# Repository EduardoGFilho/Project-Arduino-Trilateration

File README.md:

# Project-Arduino-Trilateration

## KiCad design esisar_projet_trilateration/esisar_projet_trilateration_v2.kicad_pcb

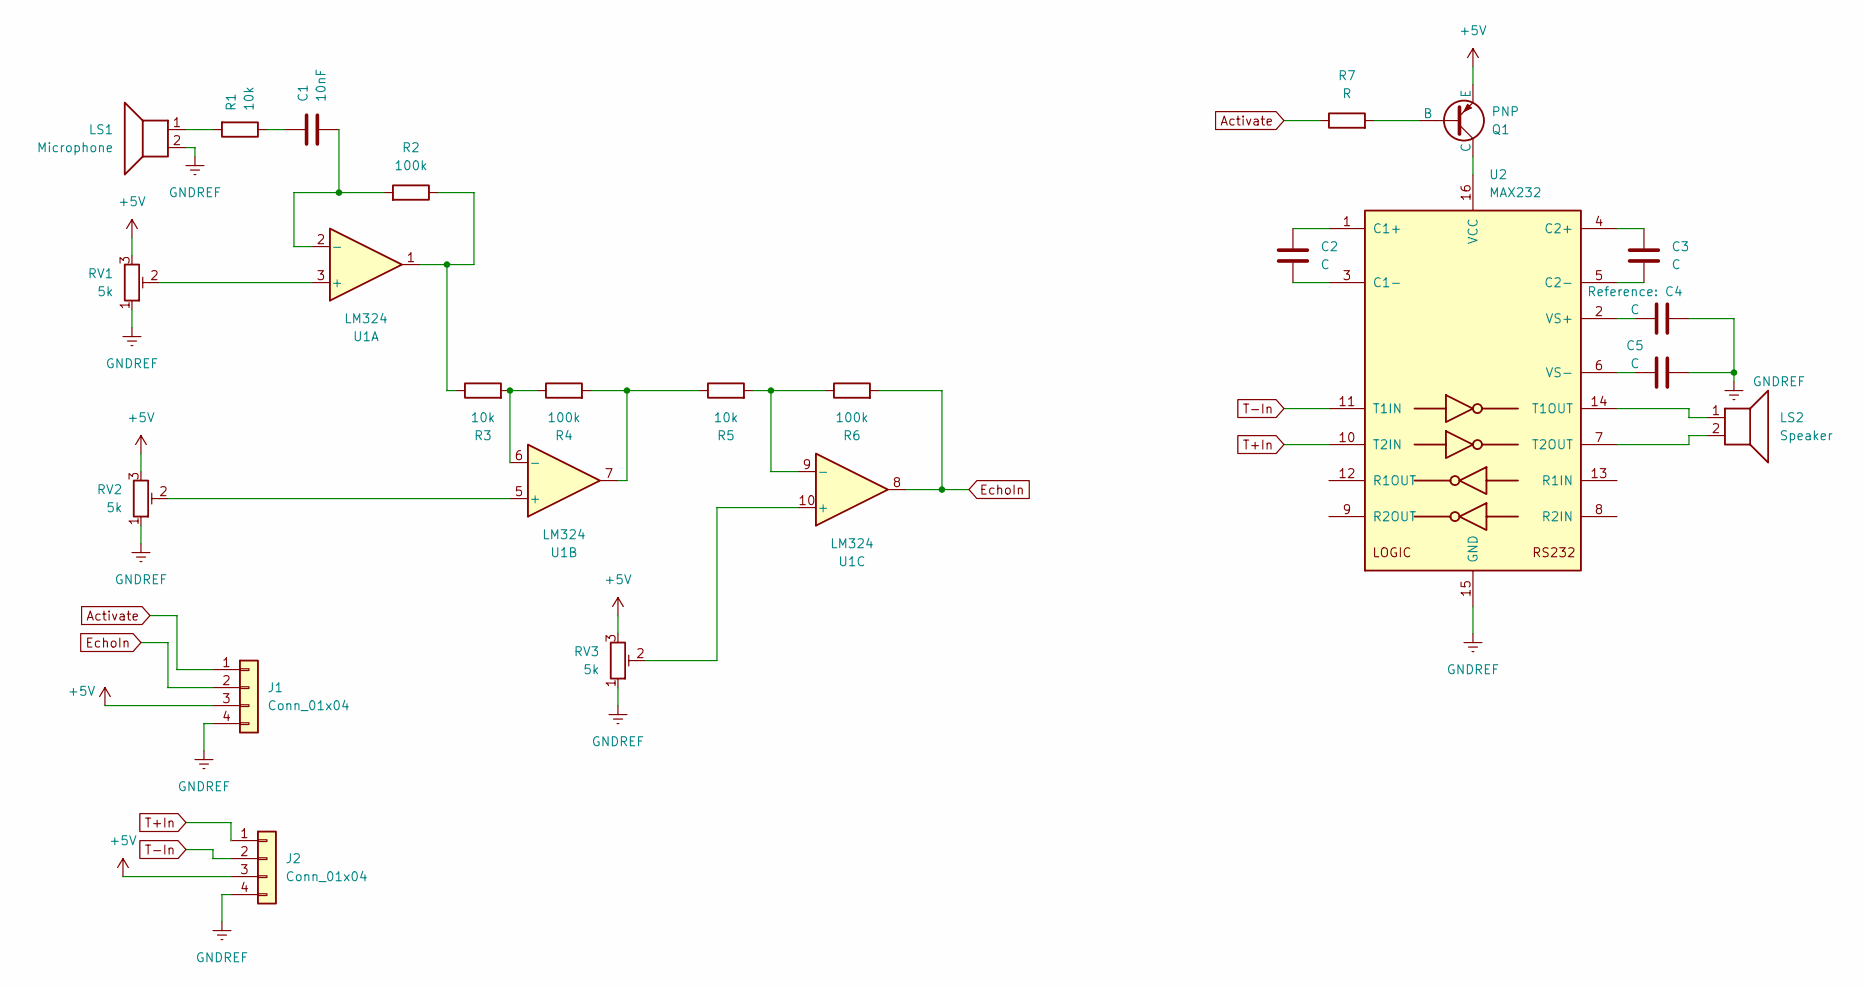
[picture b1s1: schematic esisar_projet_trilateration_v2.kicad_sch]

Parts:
C1: 10nF; C_0603_1608Metric_Pad1.08x0.95mm_HandSolder
C2, C3, C4, C5: C; C_0603_1608Metric_Pad1.08x0.95mm_HandSolder
J1, J2: Conn_01x04; JST_XH_B4B-XH-AM_1x04_P2.50mm_Vertical
LS1: Microphone; TR4010R-T
LS2: Speaker; TR4010R-T
Q1: PNP; SOT-23
R1, R3, R5: 10k; R_0603_1608Metric_Pad0.98x0.95mm_HandSolder
R2, R4, R6: 100k; R_0603_1608Metric_Pad0.98x0.95mm_HandSolder
R7: R; R_0603_1608Metric_Pad0.98x0.95mm_HandSolder
RV1, RV2, RV3: 5k; Potentiometer_ACP_CA6-VSMD_Vertical
U1: LM324; SOIC-14_3.9x8.7mm_P1.27mm
U2: MAX232; SO-16_3.9x9.9mm_P1.27mm

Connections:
+5V: J1.3, J2.3, Q1.3 (E), RV1.3, RV2.3, RV3.3
Activate: J1.1, R7.1
EchoIn: J1.2, R6.2, U1.8
GNDREF: C4.2, C5.2, J1.4, J2.4, LS1.2, RV1.1, RV2.1, RV3.1, U2.15 (GND)
unnamed: C1.1, R1.1
unnamed: LS1.1, R1.2
unnamed: Q1.2 (B), R7.2
unnamed: Q1.1 (C), U2.16 (VCC)
unnamed: R2.1, R3.1, U1.1
unnamed: R4.2, R5.1, U1.7
unnamed: RV1.2, U1.3 (+)
unnamed: C1.2, R2.2, U1.2 (-)
unnamed: RV2.2, U1.5 (+)
unnamed: R3.2, R4.1, U1.6 (-)
unnamed: RV3.2, U1.10 (+)
unnamed: R5.2, R6.1, U1.9 (-)
unnamed: C2.1, U2.1 (C1+)
unnamed: C2.2, U2.3 (C1-)
unnamed: C3.1, U2.4 (C2+)
unnamed: C3.2, U2.5 (C2-)
unnamed: LS2.1, U2.14 (T1OUT)
unnamed: LS2.2, U2.7 (T2OUT)
unnamed: C4.1, U2.2 (VS+)
unnamed: C5.1, U2.6 (VS-)
T+In: J2.1, U2.10 (T2IN)
T-In: J2.2, U2.11 (T1IN)

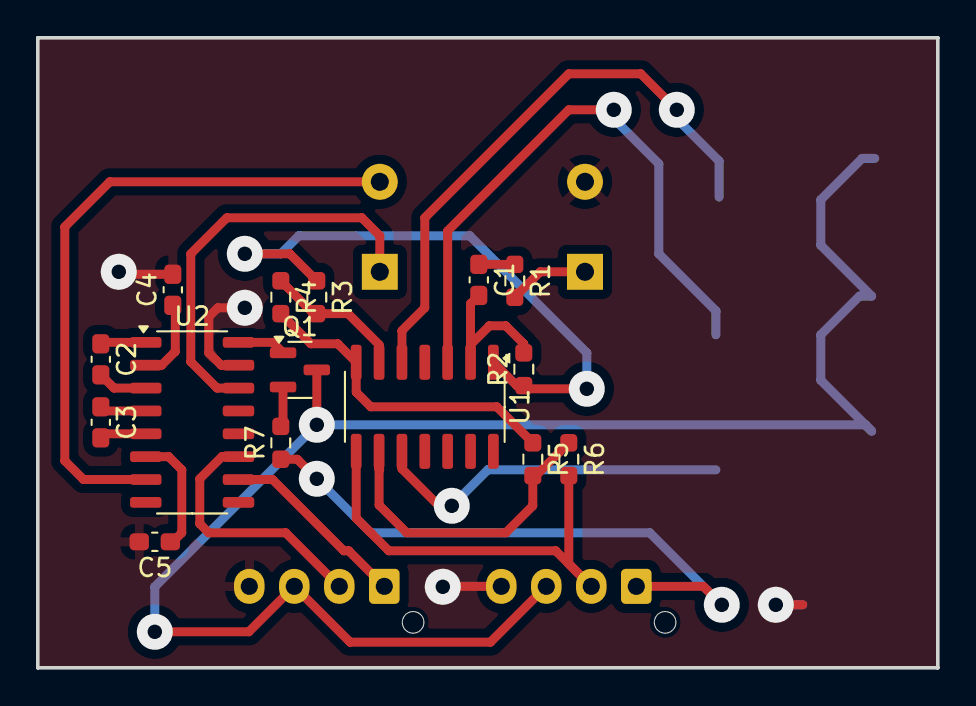
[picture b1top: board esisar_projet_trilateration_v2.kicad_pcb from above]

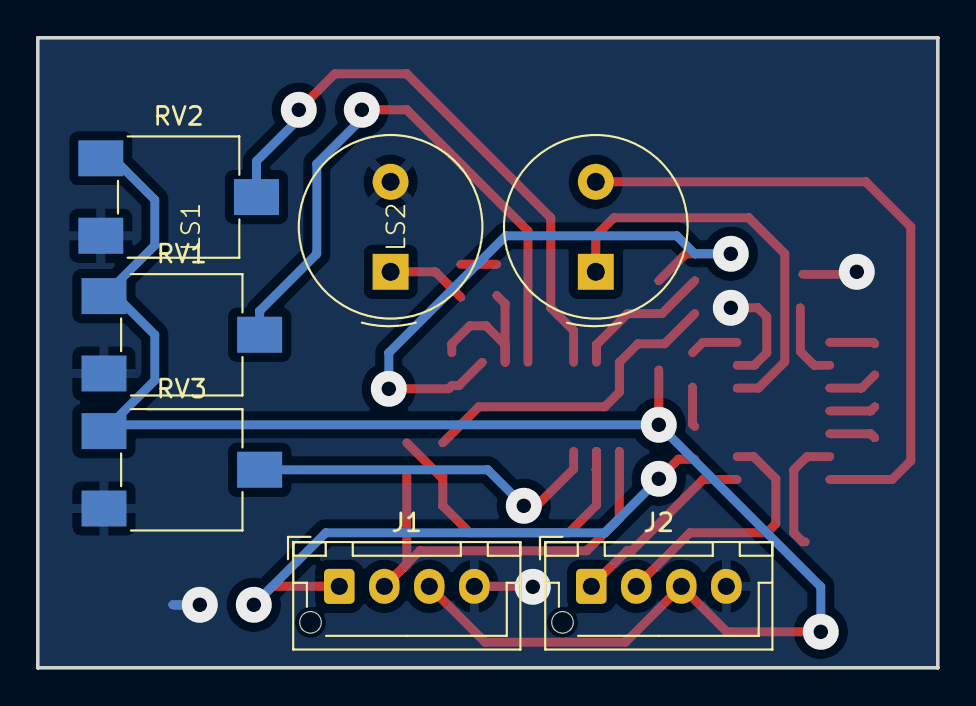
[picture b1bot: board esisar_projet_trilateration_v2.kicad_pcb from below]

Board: 2 copper layers, 50.0 x 35.0 mm, 22 parts (7 on the bottom side), 26 nets.

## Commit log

2024-10-11 Add kicad project
2024-12-05 Code organization
2024-12-06 Add arduino capture code
2024-12-06 Clean kicad project
